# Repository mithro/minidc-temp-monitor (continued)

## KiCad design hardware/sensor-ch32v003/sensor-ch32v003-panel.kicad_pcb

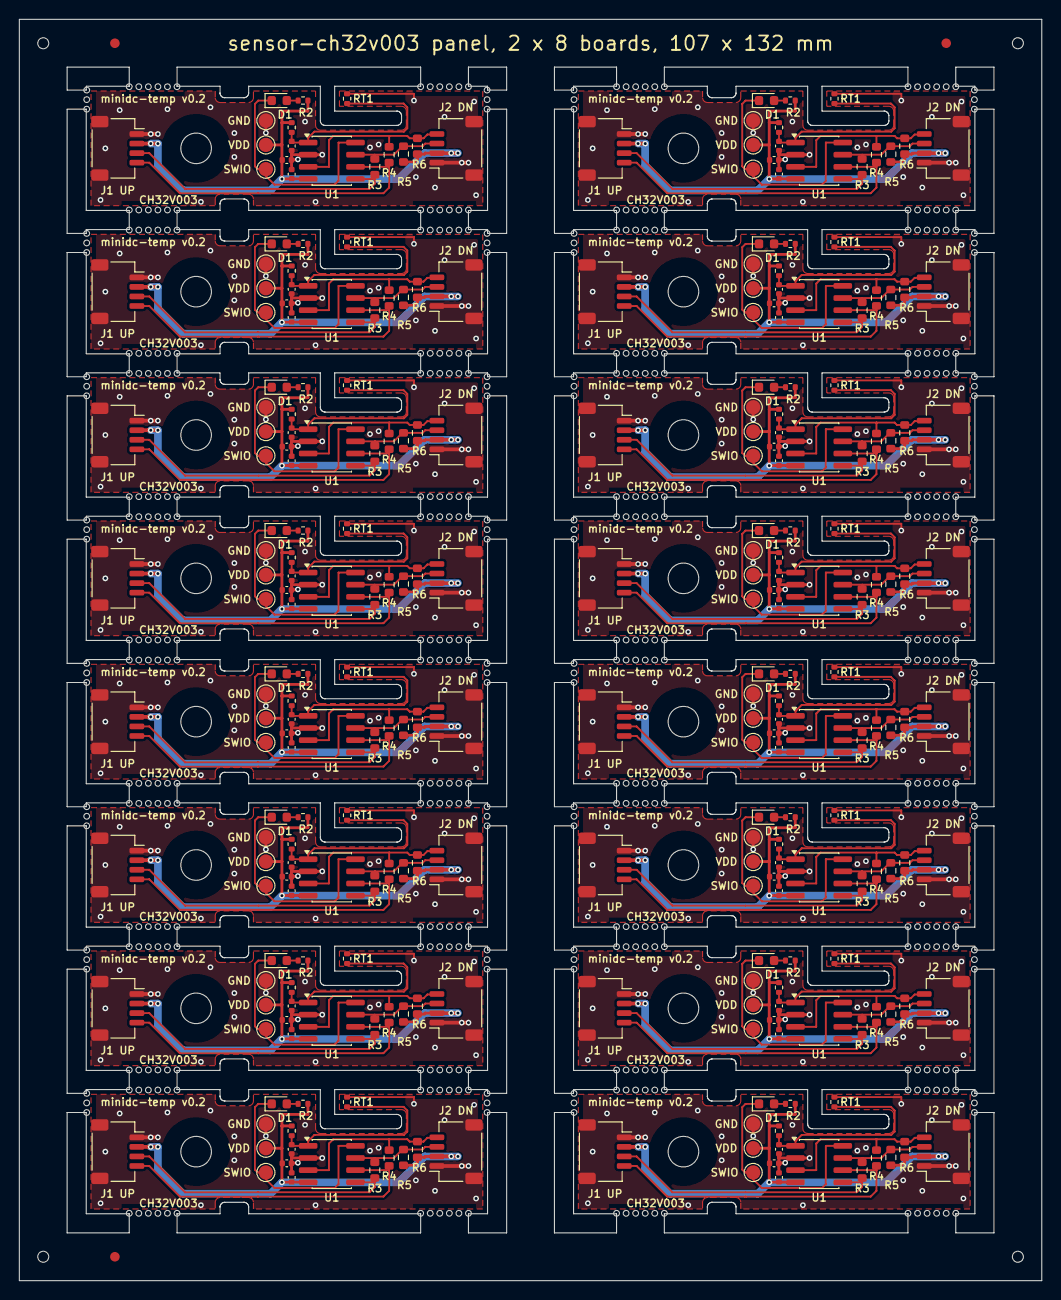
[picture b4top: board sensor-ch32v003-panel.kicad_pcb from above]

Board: 2 copper layers, 107.0 x 132.0 mm, 288 parts (0 on the bottom side), 144 nets.

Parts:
C1_01, C1_02, C1_03, C1_04, C1_05, C1_06, C1_07, C1_08, C1_09, C1_10, C1_11, C1_12, C1_13, C1_14, C1_15, C1_16, C3_01, C3_02, C3_03, C3_04, C3_05, C3_06, C3_07, C3_08, C3_09, C3_10, C3_11, C3_12, C3_13, C3_14, C3_15, C3_16: 100n; C_0402_1005Metric
C2_01, C2_02, C2_03, C2_04, C2_05, C2_06, C2_07, C2_08, C2_09, C2_10, C2_11, C2_12, C2_13, C2_14, C2_15, C2_16: 1u; C_0402_1005Metric
D1_01, D1_02, D1_03, D1_04, D1_05, D1_06, D1_07, D1_08, D1_09, D1_10, D1_11, D1_12, D1_13, D1_14, D1_15, D1_16: RED; LED_0603_1608Metric
H1_01, H1_02, H1_03, H1_04, H1_05, H1_06, H1_07, H1_08, H1_09, H1_10, H1_11, H1_12, H1_13, H1_14, H1_15, H1_16: M3; MountingHole_3.2mm_M3
J1_01, J1_02, J1_03, J1_04, J1_05, J1_06, J1_07, J1_08, J1_09, J1_10, J1_11, J1_12, J1_13, J1_14, J1_15, J1_16: Qwiic UP; JST_SH_SM04B-SRSS-TB_1x04-1MP_P1.00mm_Horizontal
J2_01, J2_02, J2_03, J2_04, J2_05, J2_06, J2_07, J2_08, J2_09, J2_10, J2_11, J2_12, J2_13, J2_14, J2_15, J2_16: Qwiic DOWN; JST_SH_SM04B-SRSS-TB_1x04-1MP_P1.00mm_Horizontal
R1_01, R1_02, R1_03, R1_04, R1_05, R1_06, R1_07, R1_08, R1_09, R1_10, R1_11, R1_12, R1_13, R1_14, R1_15, R1_16: 100k 1%; R_0402_1005Metric
R2_01, R2_02, R2_03, R2_04, R2_05, R2_06, R2_07, R2_08, R2_09, R2_10, R2_11, R2_12, R2_13, R2_14, R2_15, R2_16: 1k; R_0402_1005Metric
R3_01, R3_02, R3_03, R3_04, R3_05, R3_06, R3_07, R3_08, R3_09, R3_10, R3_11, R3_12, R3_13, R3_14, R3_15, R3_16, R4_01, R4_02, R4_03, R4_04, R4_05, R4_06, R4_07, R4_08, R4_09, R4_10, R4_11, R4_12, R4_13, R4_14, R4_15, R4_16: 0R; R_0603_1608Metric
R5_01, R5_02, R5_03, R5_04, R5_05, R5_06, R5_07, R5_08, R5_09, R5_10, R5_11, R5_12, R5_13, R5_14, R5_15, R5_16, R6_01, R6_02, R6_03, R6_04, R6_05, R6_06, R6_07, R6_08, R6_09, R6_10, R6_11, R6_12, R6_13, R6_14, R6_15, R6_16: 4k7; R_0603_1608Metric
RT1_01, RT1_02, RT1_03, RT1_04, RT1_05, RT1_06, RT1_07, RT1_08, RT1_09, RT1_10, RT1_11, RT1_12, RT1_13, RT1_14, RT1_15, RT1_16: 100k B3950 1%; R_0402_1005Metric
TP1_01, TP1_02, TP1_03, TP1_04, TP1_05, TP1_06, TP1_07, TP1_08, TP1_09, TP1_10, TP1_11, TP1_12, TP1_13, TP1_14, TP1_15, TP1_16: SWIO; TestPoint_Pad_D1.5mm
TP2_01, TP2_02, TP2_03, TP2_04, TP2_05, TP2_06, TP2_07, TP2_08, TP2_09, TP2_10, TP2_11, TP2_12, TP2_13, TP2_14, TP2_15, TP2_16: VDD; TestPoint_Pad_D1.5mm
TP3_01, TP3_02, TP3_03, TP3_04, TP3_05, TP3_06, TP3_07, TP3_08, TP3_09, TP3_10, TP3_11, TP3_12, TP3_13, TP3_14, TP3_15, TP3_16: GND; TestPoint_Pad_D1.5mm
U1_01, U1_02, U1_03, U1_04, U1_05, U1_06, U1_07, U1_08, U1_09, U1_10, U1_11, U1_12, U1_13, U1_14, U1_15, U1_16: CH32V003J4M6; SOIC-8_3.9x4.9mm_P1.27mm

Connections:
B01/GND: C1_01.2, C2_01.2, C3_01.2, J1_01.1, J1_01.MP, J2_01.1, J2_01.MP, RT1_01.2, TP3_01.1, U1_01.2
B01/NTC_ADC: C3_01.1, R1_01.2, RT1_01.1, U1_01.1
B01/Net-(D1-A): D1_01.2, R2_01.2
B01/SCL_DN: J2_01.4, R4_01.2, R6_01.2, U1_01.3
B01/SCL_UP: J1_01.4, R4_01.1, U1_01.6
B01/SDA_DN: J2_01.3, R3_01.2, R5_01.2, U1_01.7
B01/SDA_UP: J1_01.3, R3_01.1, U1_01.5
B01/SWIO: D1_01.1, TP1_01.1, U1_01.8
B01/VDD: C1_01.1, C2_01.1, J1_01.2, J2_01.2, R1_01.1, R2_01.1, R5_01.1, R6_01.1, TP2_01.1, U1_01.4
B02/GND: C1_02.2, C2_02.2, C3_02.2, J1_02.1, J1_02.MP, J2_02.1, J2_02.MP, RT1_02.2, TP3_02.1, U1_02.2
B02/NTC_ADC: C3_02.1, R1_02.2, RT1_02.1, U1_02.1
B02/Net-(D1-A): D1_02.2, R2_02.2
B02/SCL_DN: J2_02.4, R4_02.2, R6_02.2, U1_02.3
B02/SCL_UP: J1_02.4, R4_02.1, U1_02.6
B02/SDA_DN: J2_02.3, R3_02.2, R5_02.2, U1_02.7
B02/SDA_UP: J1_02.3, R3_02.1, U1_02.5
B02/SWIO: D1_02.1, TP1_02.1, U1_02.8
B02/VDD: C1_02.1, C2_02.1, J1_02.2, J2_02.2, R1_02.1, R2_02.1, R5_02.1, R6_02.1, TP2_02.1, U1_02.4
B03/GND: C1_03.2, C2_03.2, C3_03.2, J1_03.1, J1_03.MP, J2_03.1, J2_03.MP, RT1_03.2, TP3_03.1, U1_03.2
B03/NTC_ADC: C3_03.1, R1_03.2, RT1_03.1, U1_03.1
B03/Net-(D1-A): D1_03.2, R2_03.2
B03/SCL_DN: J2_03.4, R4_03.2, R6_03.2, U1_03.3
B03/SCL_UP: J1_03.4, R4_03.1, U1_03.6
B03/SDA_DN: J2_03.3, R3_03.2, R5_03.2, U1_03.7
B03/SDA_UP: J1_03.3, R3_03.1, U1_03.5
B03/SWIO: D1_03.1, TP1_03.1, U1_03.8
B03/VDD: C1_03.1, C2_03.1, J1_03.2, J2_03.2, R1_03.1, R2_03.1, R5_03.1, R6_03.1, TP2_03.1, U1_03.4
B04/GND: C1_04.2, C2_04.2, C3_04.2, J1_04.1, J1_04.MP, J2_04.1, J2_04.MP, RT1_04.2, TP3_04.1, U1_04.2
B04/NTC_ADC: C3_04.1, R1_04.2, RT1_04.1, U1_04.1
B04/Net-(D1-A): D1_04.2, R2_04.2
B04/SCL_DN: J2_04.4, R4_04.2, R6_04.2, U1_04.3
B04/SCL_UP: J1_04.4, R4_04.1, U1_04.6
B04/SDA_DN: J2_04.3, R3_04.2, R5_04.2, U1_04.7
B04/SDA_UP: J1_04.3, R3_04.1, U1_04.5
B04/SWIO: D1_04.1, TP1_04.1, U1_04.8
B04/VDD: C1_04.1, C2_04.1, J1_04.2, J2_04.2, R1_04.1, R2_04.1, R5_04.1, R6_04.1, TP2_04.1, U1_04.4
B05/GND: C1_05.2, C2_05.2, C3_05.2, J1_05.1, J1_05.MP, J2_05.1, J2_05.MP, RT1_05.2, TP3_05.1, U1_05.2
B05/NTC_ADC: C3_05.1, R1_05.2, RT1_05.1, U1_05.1
B05/Net-(D1-A): D1_05.2, R2_05.2
B05/SCL_DN: J2_05.4, R4_05.2, R6_05.2, U1_05.3
B05/SCL_UP: J1_05.4, R4_05.1, U1_05.6
B05/SDA_DN: J2_05.3, R3_05.2, R5_05.2, U1_05.7
B05/SDA_UP: J1_05.3, R3_05.1, U1_05.5
B05/SWIO: D1_05.1, TP1_05.1, U1_05.8
B05/VDD: C1_05.1, C2_05.1, J1_05.2, J2_05.2, R1_05.1, R2_05.1, R5_05.1, R6_05.1, TP2_05.1, U1_05.4
B06/GND: C1_06.2, C2_06.2, C3_06.2, J1_06.1, J1_06.MP, J2_06.1, J2_06.MP, RT1_06.2, TP3_06.1, U1_06.2
B06/NTC_ADC: C3_06.1, R1_06.2, RT1_06.1, U1_06.1
B06/Net-(D1-A): D1_06.2, R2_06.2
B06/SCL_DN: J2_06.4, R4_06.2, R6_06.2, U1_06.3
B06/SCL_UP: J1_06.4, R4_06.1, U1_06.6
B06/SDA_DN: J2_06.3, R3_06.2, R5_06.2, U1_06.7
B06/SDA_UP: J1_06.3, R3_06.1, U1_06.5
B06/SWIO: D1_06.1, TP1_06.1, U1_06.8
B06/VDD: C1_06.1, C2_06.1, J1_06.2, J2_06.2, R1_06.1, R2_06.1, R5_06.1, R6_06.1, TP2_06.1, U1_06.4
B07/GND: C1_07.2, C2_07.2, C3_07.2, J1_07.1, J1_07.MP, J2_07.1, J2_07.MP, RT1_07.2, TP3_07.1, U1_07.2
B07/NTC_ADC: C3_07.1, R1_07.2, RT1_07.1, U1_07.1
B07/Net-(D1-A): D1_07.2, R2_07.2
B07/SCL_DN: J2_07.4, R4_07.2, R6_07.2, U1_07.3
B07/SCL_UP: J1_07.4, R4_07.1, U1_07.6
B07/SDA_DN: J2_07.3, R3_07.2, R5_07.2, U1_07.7
B07/SDA_UP: J1_07.3, R3_07.1, U1_07.5
B07/SWIO: D1_07.1, TP1_07.1, U1_07.8
B07/VDD: C1_07.1, C2_07.1, J1_07.2, J2_07.2, R1_07.1, R2_07.1, R5_07.1, R6_07.1, TP2_07.1, U1_07.4
B08/GND: C1_08.2, C2_08.2, C3_08.2, J1_08.1, J1_08.MP, J2_08.1, J2_08.MP, RT1_08.2, TP3_08.1, U1_08.2
B08/NTC_ADC: C3_08.1, R1_08.2, RT1_08.1, U1_08.1
B08/Net-(D1-A): D1_08.2, R2_08.2
B08/SCL_DN: J2_08.4, R4_08.2, R6_08.2, U1_08.3
B08/SCL_UP: J1_08.4, R4_08.1, U1_08.6
B08/SDA_DN: J2_08.3, R3_08.2, R5_08.2, U1_08.7
B08/SDA_UP: J1_08.3, R3_08.1, U1_08.5
B08/SWIO: D1_08.1, TP1_08.1, U1_08.8
B08/VDD: C1_08.1, C2_08.1, J1_08.2, J2_08.2, R1_08.1, R2_08.1, R5_08.1, R6_08.1, TP2_08.1, U1_08.4
B09/GND: C1_09.2, C2_09.2, C3_09.2, J1_09.1, J1_09.MP, J2_09.1, J2_09.MP, RT1_09.2, TP3_09.1, U1_09.2
B09/NTC_ADC: C3_09.1, R1_09.2, RT1_09.1, U1_09.1
B09/Net-(D1-A): D1_09.2, R2_09.2
B09/SCL_DN: J2_09.4, R4_09.2, R6_09.2, U1_09.3
B09/SCL_UP: J1_09.4, R4_09.1, U1_09.6
B09/SDA_DN: J2_09.3, R3_09.2, R5_09.2, U1_09.7
B09/SDA_UP: J1_09.3, R3_09.1, U1_09.5
B09/SWIO: D1_09.1, TP1_09.1, U1_09.8
B09/VDD: C1_09.1, C2_09.1, J1_09.2, J2_09.2, R1_09.1, R2_09.1, R5_09.1, R6_09.1, TP2_09.1, U1_09.4
B10/GND: C1_10.2, C2_10.2, C3_10.2, J1_10.1, J1_10.MP, J2_10.1, J2_10.MP, RT1_10.2, TP3_10.1, U1_10.2
B10/NTC_ADC: C3_10.1, R1_10.2, RT1_10.1, U1_10.1
B10/Net-(D1-A): D1_10.2, R2_10.2
B10/SCL_DN: J2_10.4, R4_10.2, R6_10.2, U1_10.3
B10/SCL_UP: J1_10.4, R4_10.1, U1_10.6
B10/SDA_DN: J2_10.3, R3_10.2, R5_10.2, U1_10.7
B10/SDA_UP: J1_10.3, R3_10.1, U1_10.5
B10/SWIO: D1_10.1, TP1_10.1, U1_10.8
B10/VDD: C1_10.1, C2_10.1, J1_10.2, J2_10.2, R1_10.1, R2_10.1, R5_10.1, R6_10.1, TP2_10.1, U1_10.4
B11/GND: C1_11.2, C2_11.2, C3_11.2, J1_11.1, J1_11.MP, J2_11.1, J2_11.MP, RT1_11.2, TP3_11.1, U1_11.2
B11/NTC_ADC: C3_11.1, R1_11.2, RT1_11.1, U1_11.1
B11/Net-(D1-A): D1_11.2, R2_11.2
B11/SCL_DN: J2_11.4, R4_11.2, R6_11.2, U1_11.3
B11/SCL_UP: J1_11.4, R4_11.1, U1_11.6
B11/SDA_DN: J2_11.3, R3_11.2, R5_11.2, U1_11.7
B11/SDA_UP: J1_11.3, R3_11.1, U1_11.5
B11/SWIO: D1_11.1, TP1_11.1, U1_11.8
B11/VDD: C1_11.1, C2_11.1, J1_11.2, J2_11.2, R1_11.1, R2_11.1, R5_11.1, R6_11.1, TP2_11.1, U1_11.4
B12/GND: C1_12.2, C2_12.2, C3_12.2, J1_12.1, J1_12.MP, J2_12.1, J2_12.MP, RT1_12.2, TP3_12.1, U1_12.2
B12/NTC_ADC: C3_12.1, R1_12.2, RT1_12.1, U1_12.1
B12/Net-(D1-A): D1_12.2, R2_12.2
B12/SCL_DN: J2_12.4, R4_12.2, R6_12.2, U1_12.3
B12/SCL_UP: J1_12.4, R4_12.1, U1_12.6
B12/SDA_DN: J2_12.3, R3_12.2, R5_12.2, U1_12.7
B12/SDA_UP: J1_12.3, R3_12.1, U1_12.5
B12/SWIO: D1_12.1, TP1_12.1, U1_12.8
B12/VDD: C1_12.1, C2_12.1, J1_12.2, J2_12.2, R1_12.1, R2_12.1, R5_12.1, R6_12.1, TP2_12.1, U1_12.4
B13/GND: C1_13.2, C2_13.2, C3_13.2, J1_13.1, J1_13.MP, J2_13.1, J2_13.MP, RT1_13.2, TP3_13.1, U1_13.2
B13/NTC_ADC: C3_13.1, R1_13.2, RT1_13.1, U1_13.1
B13/Net-(D1-A): D1_13.2, R2_13.2
B13/SCL_DN: J2_13.4, R4_13.2, R6_13.2, U1_13.3
B13/SCL_UP: J1_13.4, R4_13.1, U1_13.6
B13/SDA_DN: J2_13.3, R3_13.2, R5_13.2, U1_13.7
B13/SDA_UP: J1_13.3, R3_13.1, U1_13.5
B13/SWIO: D1_13.1, TP1_13.1, U1_13.8
B13/VDD: C1_13.1, C2_13.1, J1_13.2, J2_13.2, R1_13.1, R2_13.1, R5_13.1, R6_13.1, TP2_13.1, U1_13.4
B14/GND: C1_14.2, C2_14.2, C3_14.2, J1_14.1, J1_14.MP, J2_14.1, J2_14.MP, RT1_14.2, TP3_14.1, U1_14.2
B14/NTC_ADC: C3_14.1, R1_14.2, RT1_14.1, U1_14.1
B14/Net-(D1-A): D1_14.2, R2_14.2
B14/SCL_DN: J2_14.4, R4_14.2, R6_14.2, U1_14.3
B14/SCL_UP: J1_14.4, R4_14.1, U1_14.6
B14/SDA_DN: J2_14.3, R3_14.2, R5_14.2, U1_14.7
B14/SDA_UP: J1_14.3, R3_14.1, U1_14.5
B14/SWIO: D1_14.1, TP1_14.1, U1_14.8
B14/VDD: C1_14.1, C2_14.1, J1_14.2, J2_14.2, R1_14.1, R2_14.1, R5_14.1, R6_14.1, TP2_14.1, U1_14.4
B15/GND: C1_15.2, C2_15.2, C3_15.2, J1_15.1, J1_15.MP, J2_15.1, J2_15.MP, RT1_15.2, TP3_15.1, U1_15.2
B15/NTC_ADC: C3_15.1, R1_15.2, RT1_15.1, U1_15.1
B15/Net-(D1-A): D1_15.2, R2_15.2
B15/SCL_DN: J2_15.4, R4_15.2, R6_15.2, U1_15.3
B15/SCL_UP: J1_15.4, R4_15.1, U1_15.6
B15/SDA_DN: J2_15.3, R3_15.2, R5_15.2, U1_15.7
B15/SDA_UP: J1_15.3, R3_15.1, U1_15.5
B15/SWIO: D1_15.1, TP1_15.1, U1_15.8
B15/VDD: C1_15.1, C2_15.1, J1_15.2, J2_15.2, R1_15.1, R2_15.1, R5_15.1, R6_15.1, TP2_15.1, U1_15.4
B16/GND: C1_16.2, C2_16.2, C3_16.2, J1_16.1, J1_16.MP, J2_16.1, J2_16.MP, RT1_16.2, TP3_16.1, U1_16.2
B16/NTC_ADC: C3_16.1, R1_16.2, RT1_16.1, U1_16.1
B16/Net-(D1-A): D1_16.2, R2_16.2
B16/SCL_DN: J2_16.4, R4_16.2, R6_16.2, U1_16.3
B16/SCL_UP: J1_16.4, R4_16.1, U1_16.6
B16/SDA_DN: J2_16.3, R3_16.2, R5_16.2, U1_16.7
B16/SDA_UP: J1_16.3, R3_16.1, U1_16.5
B16/SWIO: D1_16.1, TP1_16.1, U1_16.8
B16/VDD: C1_16.1, C2_16.1, J1_16.2, J2_16.2, R1_16.1, R2_16.1, R5_16.1, R6_16.1, TP2_16.1, U1_16.4

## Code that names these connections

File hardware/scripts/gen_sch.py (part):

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        title='Temp sensor strip, CH32V003J4M6',
        parts={'U1': ('MCU_WCH_RiscV', 'CH32V003JxMx', 'CH32V003J4M6', 'Package_SO:SOIC-8_3.9x4.9mm_P1.27mm', 'C5346354', False),
               'TP1': ('Connector', 'TestPoint', 'SWIO', FP_TP, '', False)},
        pins={'U1': {'5': 'SDA_UP', '6': 'SCL_UP', '7': 'SDA_DN', '4': 'VDD', '2': 'GND',
                     '8': 'SWIO', '1': 'NTC_ADC', '3': 'SCL_DN'},
              'R1': {'1': 'VDD', '2': 'NTC_ADC'}, 'D1': {'1': 'SWIO'}, 'TP1': {'1': 'SWIO'}},
        notes=[
            'U1 pin use: PC1/PC2 = hardware I2C to the upstream connector J1.',
            'PC4 (SDA) and PA2 (SCL) = bit-banged I2C controller to J2, used only in relay mode.',
            'PA1 = ADC channel 1 on the thermistor divider; PD6 shares the pin and stays an input.',
            'PD1 = SWIO programming pin, shared with the identify LED (drive PD4 or PD5 low to light it).',
        ],
    ),
    'ch32v005': dict(
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               'TP4': ('Connector', 'TestPoint', 'NRST', FP_TP_SMALL, '', False),
               'TP5': ('Connector', 'TestPoint', 'AUX_A1', FP_TP_SMALL, '', False),
               'TP6': ('Connector', 'TestPoint', 'AUX_PC7', FP_TP_SMALL, '', False)},
        pins={'U1': {'4': 'VDD', '13': 'GND', '3': 'SDA_UP', '10': 'SCL_UP', '5': 'SDA_DN', '6': 'SCL_DN',
                     '7': 'NTC_ADC', '8': 'NTC_DRV', '2': 'LED_K', '1': 'AUX_A1', '9': 'AUX_PC7',
                     '11': None, '12': 'NRST'},
              'R1': {'1': 'NTC_DRV', '2': 'NTC_ADC'}, 'D1': {'1': 'LED_K'},
              'TP1': {'1': 'SCL_UP'}, 'TP4': {'1': 'NRST'}, 'TP5': {'1': 'AUX_A1'}, 'TP6': {'1': 'AUX_PC7'}},
        notes=[
            'U1 pin use: PD0/PD1 = hardware I2C (remap 1) to the upstream connector J1.',
            'PD1 is also SWIO, so the board is programmed through J1 pin 4 (SCL).',
            'PC0 and PC3 = bit-banged I2C controller to J2, used only in relay mode.',
            'PC4 = ADC channel 2 on the thermistor divider, powered from PC6 while sampling.',
            'PA2 = identify LED (active low).  PA1 (ADC channel 1) and PC7 = spare pins on pads.',
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        s.stub(j['MP'], 2.54, 'GND')
    s.wire(j1['3'][:2], r3['1'][:2]); s.wire(r3['2'][:2], j2['3'][:2])
    s.wire(j1['4'][:2], r4_['1'][:2]); s.wire(r4_['2'][:2], j2['4'][:2])
    s.label('SDA_UP', 60.96, 55.88, (1, 0)); s.label('SCL_UP', 60.96, 58.42, (1, 0))
    s.label('SDA_DN', 152.4, 55.88, (1, 0)); s.label('SCL_DN', 152.4, 58.42, (1, 0))
    s.stub(r5['1'], 2.54, 'VDD'); s.stub(r6['1'], 2.54, 'VDD')
    s.wire(r5['2'][:2], (132.08, 55.88)); s.wire(r6['2'][:2], (144.78, 58.42))
    s.text('Shared bus: fit R3 and R4 instead', 86.36, 69.85)
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        s.wire(r1['1'][:2], (217.17, 97.79), (209.55, 97.79)); s.label(net('R1', '1'), 209.55, 97.79, (-1, 0))
    mid, low = 111.76, 127.0
    s.wire(r1['2'][:2], (217.17, mid), rt['1'][:2])
    s.wire(c3['1'][:2], (240.03, mid), (209.55, mid)); s.label('NTC_ADC', 209.55, mid, (-1, 0))
    s.wire(rt['2'][:2], (217.17, low)); s.wire(c3['2'][:2], (240.03, low), (217.17, low)); s.power('GND', 217.17, low)

    # --- Test pads and mounting -----------------------------------------------------------------
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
